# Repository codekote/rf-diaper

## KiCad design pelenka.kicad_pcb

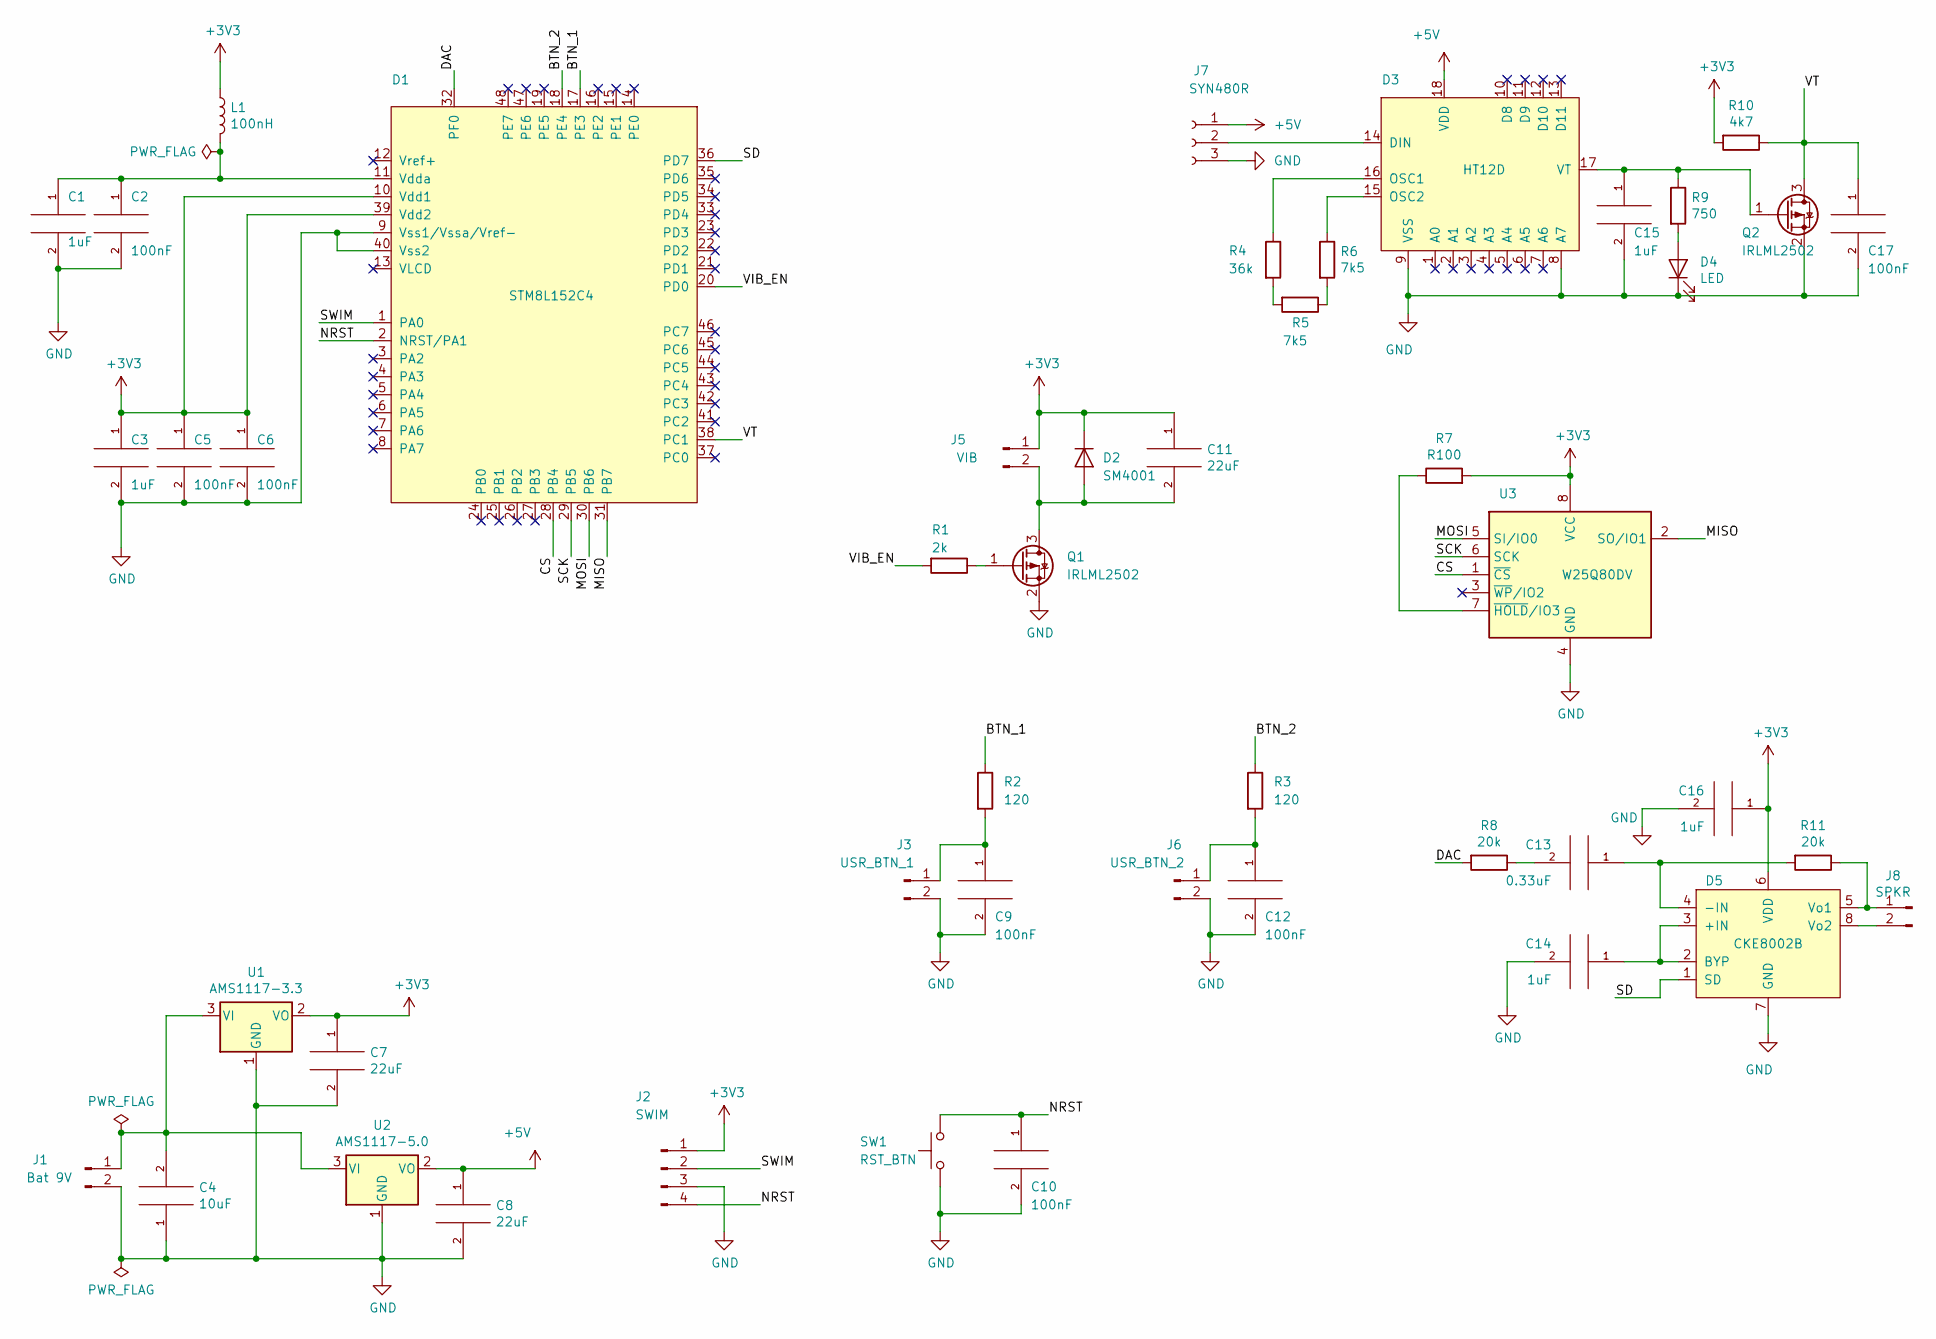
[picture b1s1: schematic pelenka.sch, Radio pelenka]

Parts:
C1, C3, C14, C15, C16: 1uF; R_1206_3216Metric_Pad1.42x1.75mm_HandSolder
C2, C5, C6, C9, C10, C12, C17: 100nF; R_1206_3216Metric_Pad1.42x1.75mm_HandSolder
C4: 10uF; R_1206_3216Metric_Pad1.42x1.75mm_HandSolder
C7, C8, C11: 22uF; R_1206_3216Metric_Pad1.42x1.75mm_HandSolder
C13: 0.33uF; R_1206_3216Metric_Pad1.42x1.75mm_HandSolder
D1: STM8L152C4; LQFP-48-1EP_7x7mm_P0.5mm_EP3.6x3.6mm
D2: SM4001; D_MELF_Handsoldering
D3: HT12D; DIP-18_W7.62mm_LongPads
D4: LED; LED_0805_2012Metric_Castellated
D5: CKE8002B; SOIC-8_3.9x4.9mm_P1.27mm
J1: Bat 9V; JST_EH_S02B-EH_1x02_P2.50mm_Horizontal
J2: SWIM; PinHeader_1x04_P2.54mm_Vertical
J3: USR_BTN_1; PinHeader_1x02_P2.54mm_Vertical
J5: VIB; JST_EH_S02B-EH_1x02_P2.50mm_Horizontal
J6: USR_BTN_2; PinHeader_1x02_P2.54mm_Vertical
J7: SYN480R; PinSocket_1x03_P2.54mm_Vertical
J8: SPKR; JST_EH_S02B-EH_1x02_P2.50mm_Horizontal
L1: 100nH; R_Axial_DIN0207_L6.3mm_D2.5mm_P10.16mm_Horizontal
Q1, Q2: IRLML2502; SOT-23
R1: 2k; R_0805_2012Metric_Pad1.15x1.40mm_HandSolder
R2, R3: 120; R_0805_2012Metric_Pad1.15x1.40mm_HandSolder
R4: 36k; R_0805_2012Metric_Pad1.15x1.40mm_HandSolder
R5, R6: 7k5; R_0805_2012Metric_Pad1.15x1.40mm_HandSolder
R7: R100; R_0805_2012Metric_Pad1.15x1.40mm_HandSolder
R8, R11: 20k; R_0805_2012Metric_Pad1.15x1.40mm_HandSolder
R9: 750; R_0805_2012Metric_Pad1.15x1.40mm_HandSolder
R10: 4k7; R_0805_2012Metric_Pad1.15x1.40mm_HandSolder
SW1: RST_BTN; SW_SPST_CK_RS282G05A3
U1: AMS1117-3.3; SOT-223-3_TabPin2
U2: AMS1117-5.0; SOT-223-3_TabPin2
U3: W25Q80DV; SOIC-8_3.9x4.9mm_P1.27mm

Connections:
+3V3: C3.1, C5.1, C6.1, C7.1, C11.1, C16.1, D1.10 (Vdd1), D1.39 (Vdd2), D2.1 (K), D5.6 (VDD), J2.1, J5.1, L1.1, R7.2, R10.2, U1.2 (VO), U3.8 (VCC)
+5V: C8.1, D3.18 (VDD), J7.1, U2.2 (VO)
/BTN_1: D1.17 (PE3), R2.1
/BTN_2: D1.18 (PE4), R3.1
/CS: D1.28 (PB4), U3.1 (~CS)
/DAC: D1.32 (PF0), R8.2
/MISO: D1.31 (PB7), U3.2 (SO/IO1)
/MOSI: D1.30 (PB6), U3.5 (SI/IO0)
/NRST: C10.1, D1.2 (NRST/PA1), J2.4, SW1.2
/SCK: D1.29 (PB5), U3.6 (SCK)
/SD: D1.36 (PD7), D5.1 (SD)
/SWIM: D1.1 (PA0), J2.2
/VIB_EN: D1.20 (PD0), R1.2
/VT: C17.1, D1.38 (PC1), Q2.3 (D), R10.1
GND: C1.2, C2.2, C3.2, C4.1, C5.2, C6.2, C7.2, C8.2, C9.2, C10.2, C12.2, C14.2, C15.2, C16.2, C17.2, D1.9 (Vss1/Vssa/Vref-), D1.40 (Vss2), D3.8 (A7), D3.9 (VSS), D4.1 (K), D5.7 (GND), J1.2, J2.3, J3.2, J6.2, J7.3, Q1.2 (S), Q2.2 (S), SW1.1, U1.1 (GND), U2.1 (GND), U3.4 (GND)
unnamed: C1.1, C2.1, D1.11 (Vdda), L1.2
unnamed: C4.2, J1.1, U1.3 (VI), U2.3 (VI)
unnamed: C9.1, J3.1, R2.2
unnamed: C11.2, D2.2 (A), J5.2, Q1.3 (D)
unnamed: C12.1, J6.1, R3.2
unnamed: C13.1, D5.4 (-IN), R11.2
unnamed: C13.2, R8.1
unnamed: C14.1, D5.2 (BYP), D5.3 (+IN)
unnamed: C15.1, D3.17 (VT), Q2.1 (G), R9.1
unnamed: D3.14 (DIN), J7.2
unnamed: D3.15 (OSC2), R6.1
unnamed: D3.16 (OSC1), R4.1
unnamed: D4.2 (A), R9.2
unnamed: D5.5 (Vo1), J8.1, R11.1
unnamed: D5.8 (Vo2), J8.2
unnamed: Q1.1 (G), R1.1
unnamed: R4.2, R5.2
unnamed: R5.1, R6.2
unnamed: R7.1, U3.7 (~HOLD~/IO3)

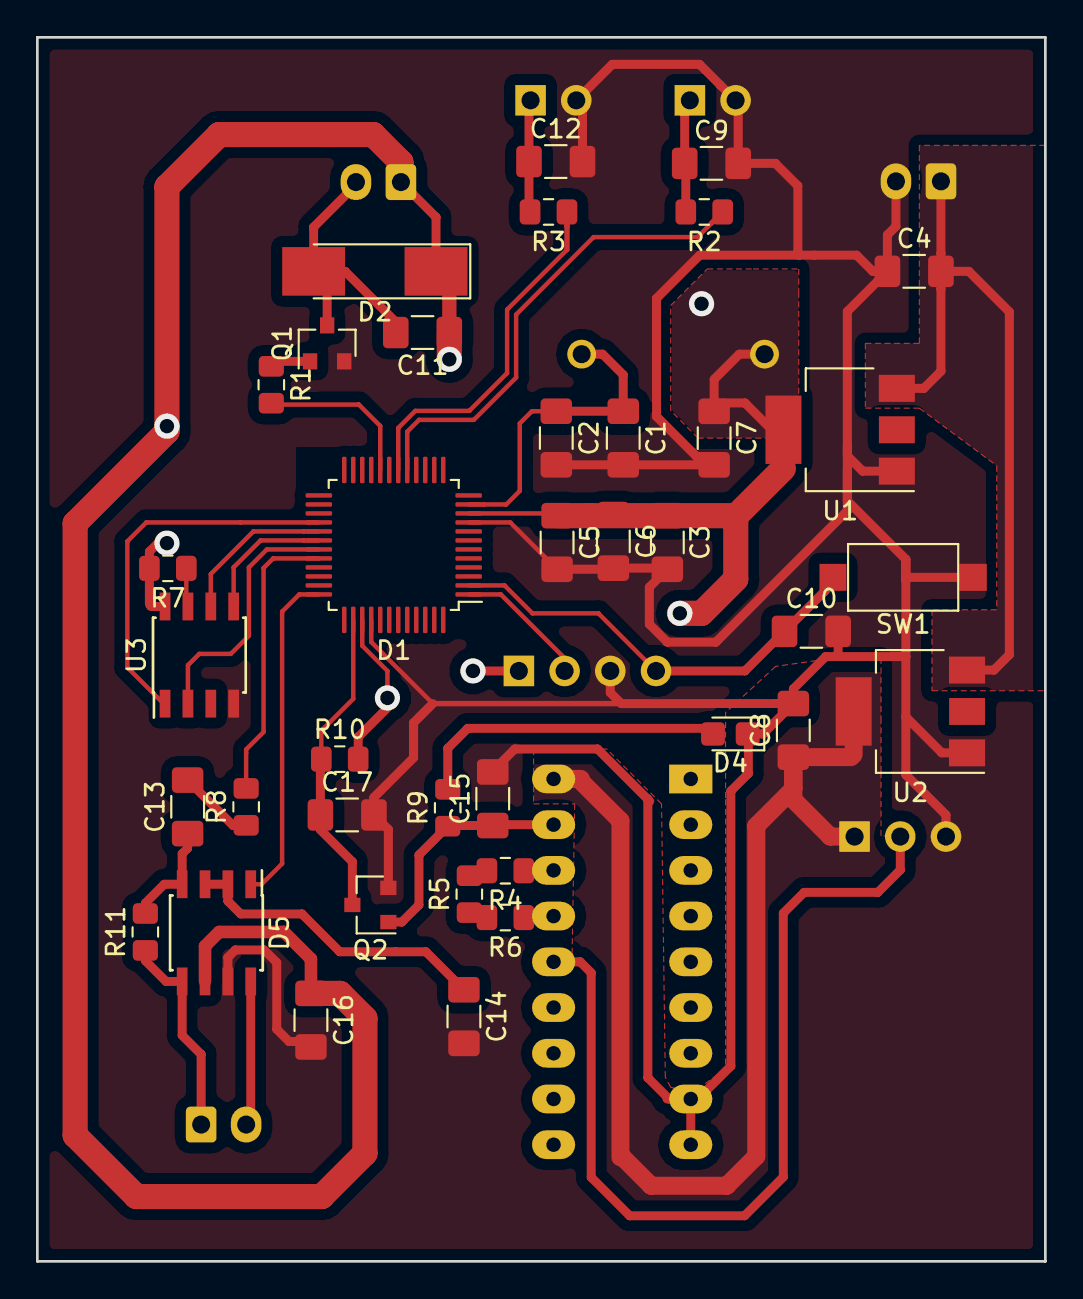
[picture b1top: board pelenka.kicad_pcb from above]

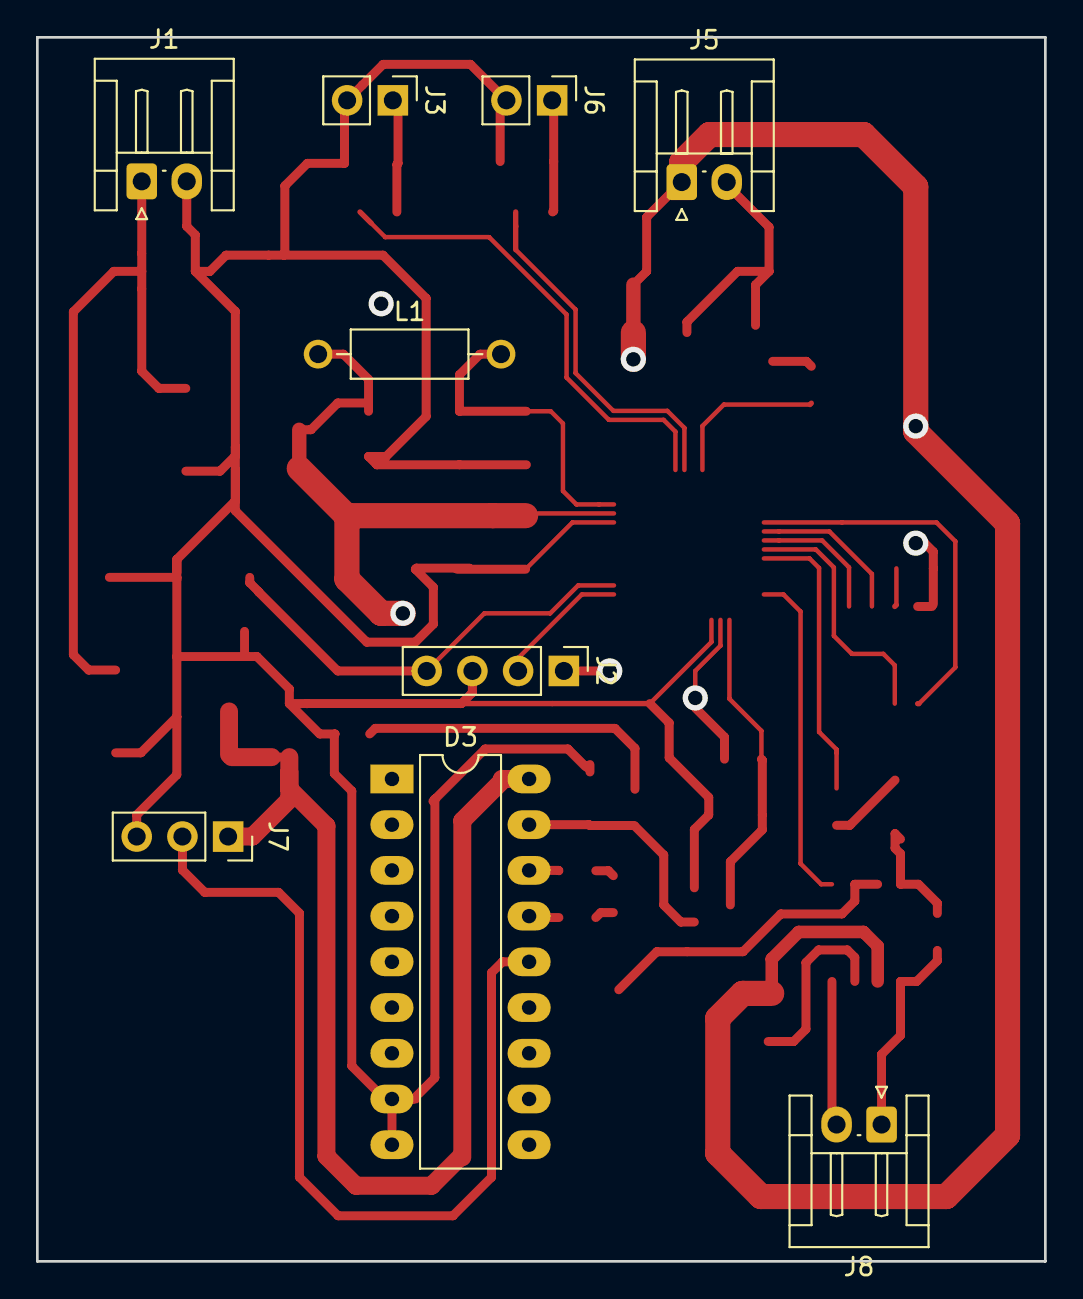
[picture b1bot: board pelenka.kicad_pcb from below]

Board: 2 copper layers, 56.0 x 68.0 mm, 47 parts (9 on the bottom side), 34 nets.

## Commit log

2020-06-29 add project
2020-08-04 fix routes padding
2020-08-05 drill holes fix
2020-08-09 add FlatCam project
